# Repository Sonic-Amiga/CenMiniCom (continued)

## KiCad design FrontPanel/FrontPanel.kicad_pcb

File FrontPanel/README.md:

# Front panel board replica

# Modifications list.

1. Modern PSUs don't output any low voltage AC, and it's much easier to just generate
the frequency needed. For the purpose this board has a 555-based simple adjustable
clock generator instead of the original buffer/phase shifter circuit.

Russian characters in this file are using UTF-8 character set.

# Assembly notes

|Original       |Replacement            |
|---------------|-----------------------|
|74LS38		|К555ЛА13		|
|74LS123	|555АГ3		        |
|NE555		|К1441ВИ1		|

# Revision history.

30.11.2022 - rev 1.0

* Errarum E001: Incorrect ground and power separation

Current - rev 2.0

- Added decoupling capacitors
- Narrowed down while maintaining compatibility with original, mounting holes are kept in the same location
- Adjusted J3 footprint so that MPW-5 connector fits in

# Contacts

Please direct all questions to pavel_fedin@mail.ru

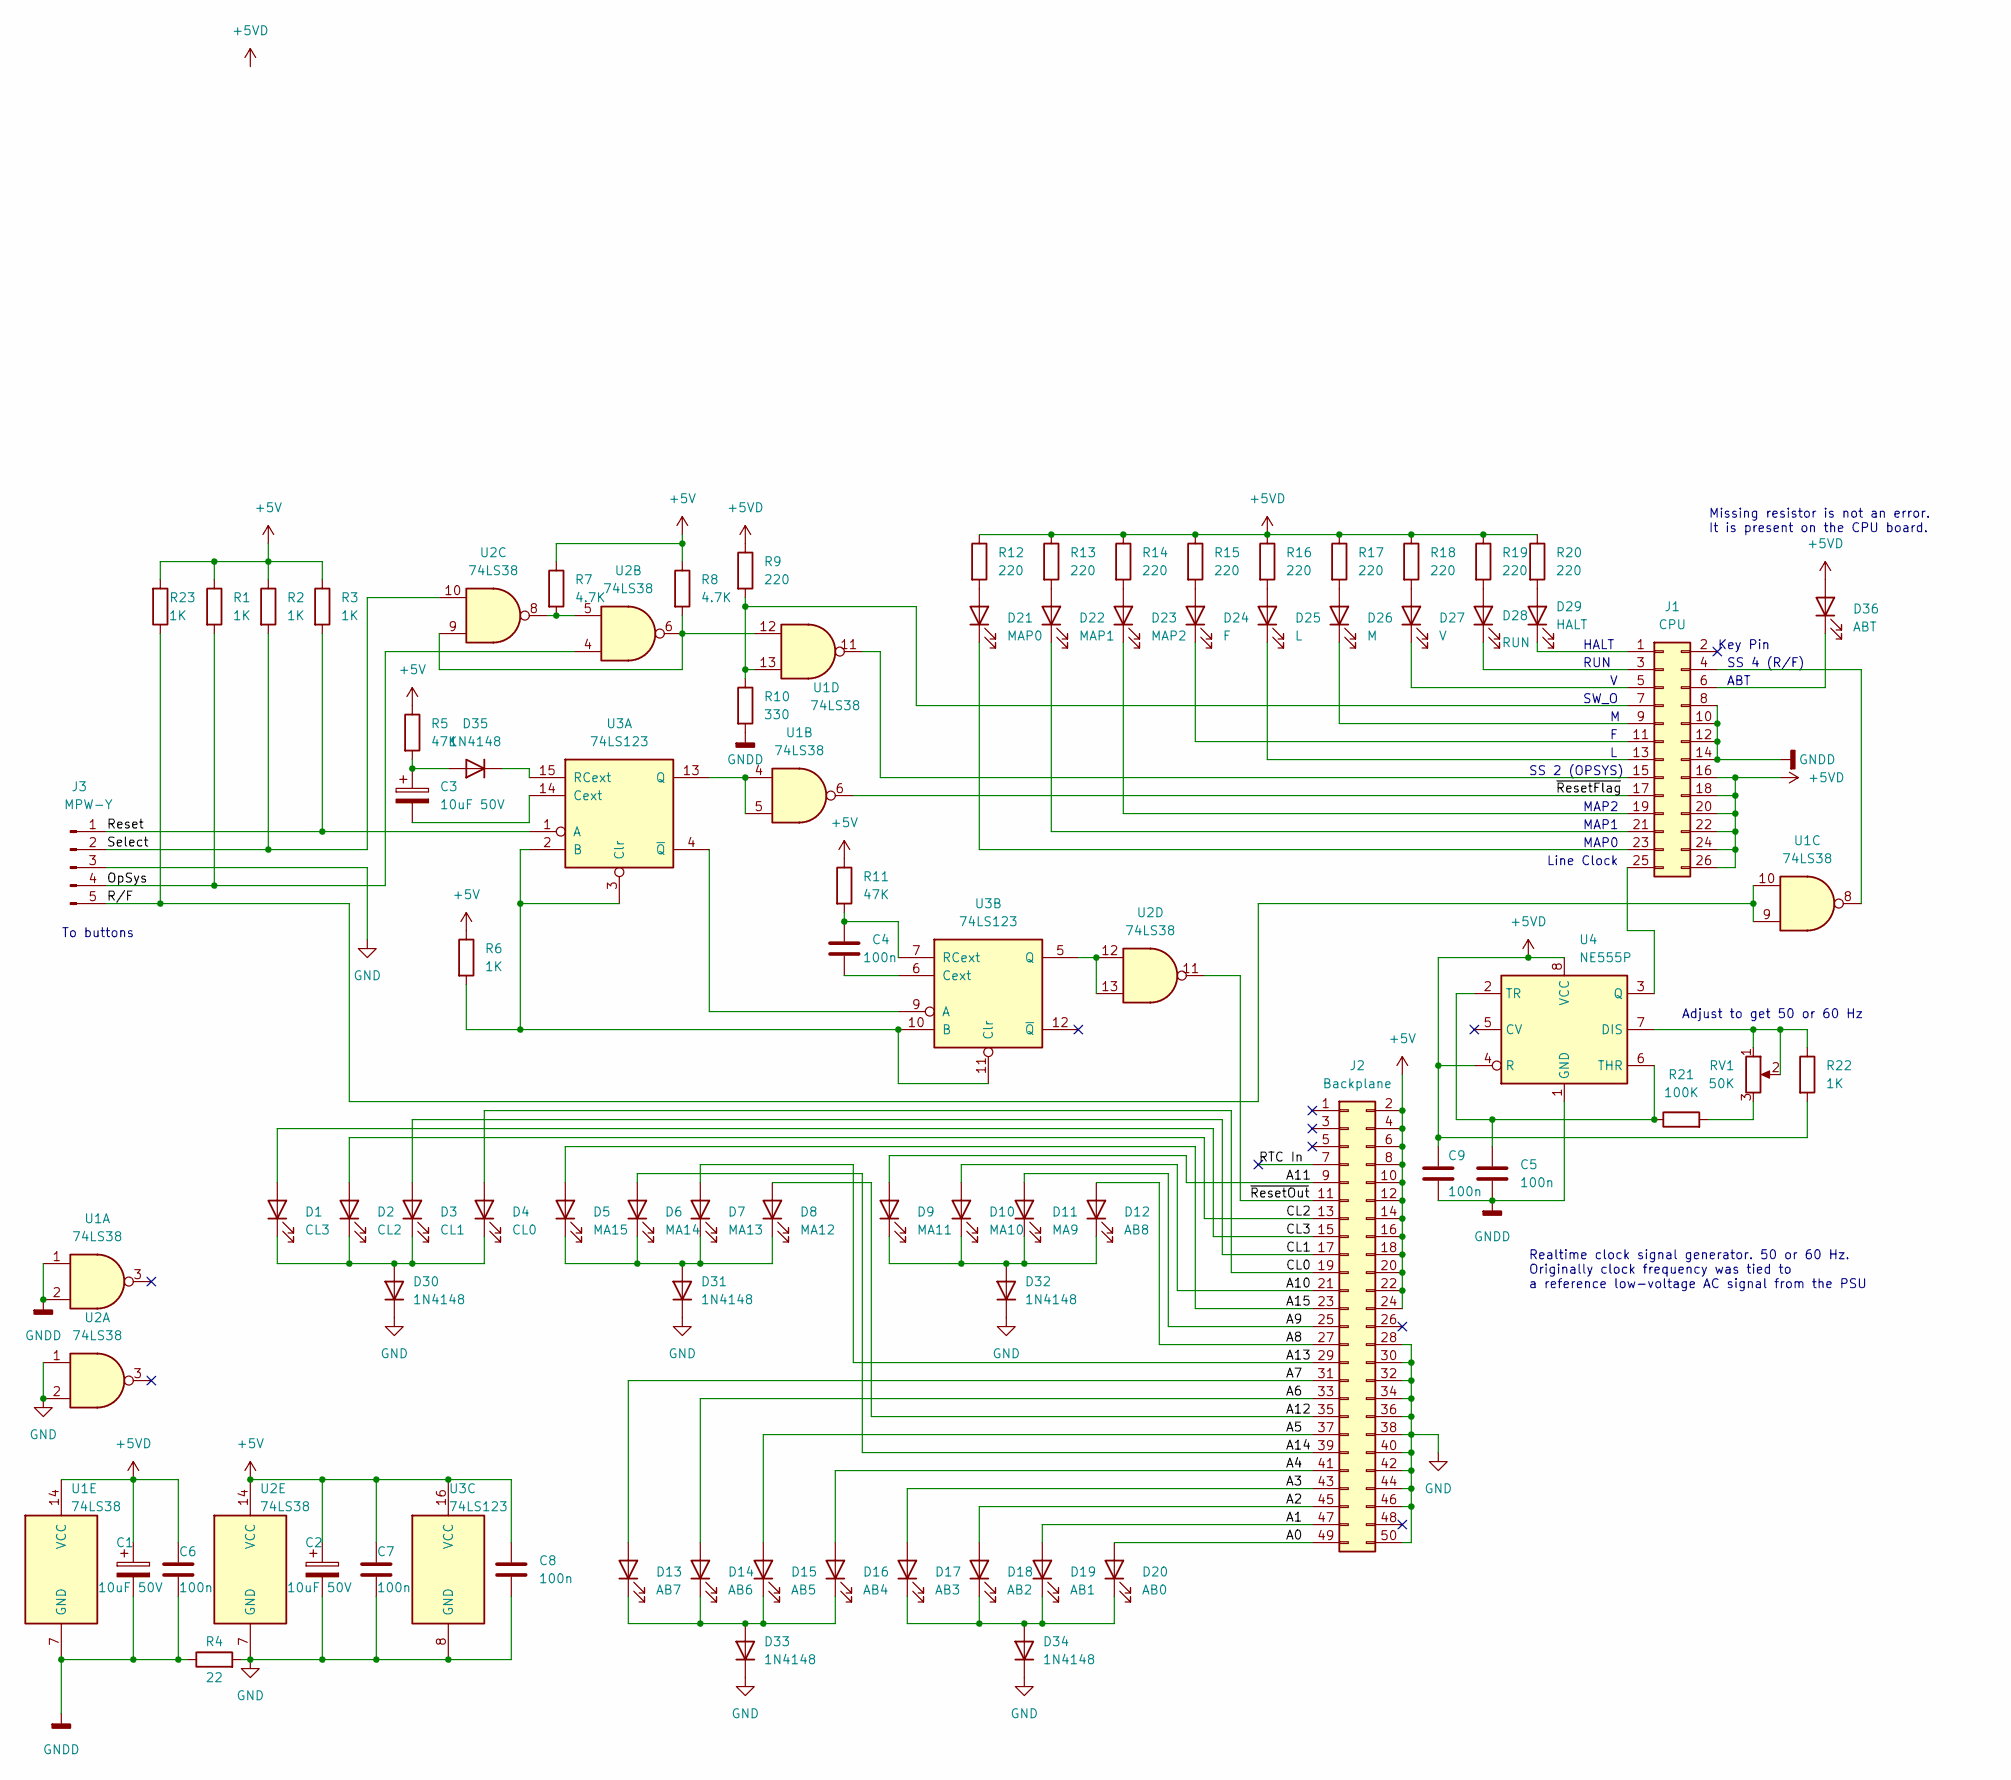
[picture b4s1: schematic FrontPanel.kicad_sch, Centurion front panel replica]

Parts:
C1, C2, C3: 10uF 50V; CP_Axial_L18.0mm_D6.5mm_P25.00mm_Horizontal
C4, C5, C6, C7, C8, C9: 100n; C_Disc_D4.3mm_W1.9mm_P5.00mm
D1: CL3; LED_D5.0mm
D2: CL2; LED_D5.0mm
D3: CL1; LED_D5.0mm
D4: CL0; LED_D5.0mm
D5: MA15; LED_D5.0mm
D6: MA14; LED_D5.0mm
D7: MA13; LED_D5.0mm
D8: MA12; LED_D5.0mm
D9: MA11; LED_D5.0mm
D10: MA10; LED_D5.0mm
D11: MA9; LED_D5.0mm
D12: AB8; LED_D5.0mm
D13: AB7; LED_D5.0mm
D14: AB6; LED_D5.0mm
D15: AB5; LED_D5.0mm
D16: AB4; LED_D5.0mm
D17: AB3; LED_D5.0mm
D18: AB2; LED_D5.0mm
D19: AB1; LED_D5.0mm
D20: AB0; LED_D5.0mm
D21: MAP0; LED_D5.0mm
D22: MAP1; LED_D5.0mm
D23: MAP2; LED_D5.0mm
D24: F; LED_D5.0mm
D25: L; LED_D5.0mm
D26: M; LED_D5.0mm
D27: V; LED_D5.0mm
D28: RUN; LED_D5.0mm
D29: HALT; LED_D5.0mm
D30, D31, D32, D33, D34, D35: 1N4148; D_A-405_P10.16mm_Horizontal
D36: ABT; LED_D5.0mm
J1: CPU; IDC-Header_2x13_P2.54mm_Vertical
J2: Backplane; IDC-Header_2x25_P2.54mm_Vertical
J3: MPW-Y; PhoenixContact_MSTBVA_2,5_5-G-5,08_1x05_P5.08mm_Vertical
R1, R2, R3, R6, R22, R23: 1K; R_Axial_DIN0207_L6.3mm_D2.5mm_P10.16mm_Horizontal
R4: 22; R_Axial_DIN0207_L6.3mm_D2.5mm_P10.16mm_Horizontal
R5, R11: 47K; R_Axial_DIN0207_L6.3mm_D2.5mm_P10.16mm_Horizontal
R7, R8: 4.7K; R_Axial_DIN0207_L6.3mm_D2.5mm_P10.16mm_Horizontal
R9, R12, R13, R14, R15, R16, R17, R18, R19, R20: 220; R_Axial_DIN0207_L6.3mm_D2.5mm_P10.16mm_Horizontal
R10: 330; R_Axial_DIN0207_L6.3mm_D2.5mm_P10.16mm_Horizontal
R21: 100K; R_Axial_DIN0207_L6.3mm_D2.5mm_P10.16mm_Horizontal
RV1: 50K; Potentiometer_Bourns_3299Y_Vertical
U1, U2: 74LS38; DIP-14_W7.62mm
U3: 74LS123; DIP-16_W7.62mm
U4: NE555P; DIP-8_W7.62mm

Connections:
+5V: C2.1, C7.1, C8.1, J2.2, J2.4, J2.6, J2.8, J2.10, J2.12, J2.14, J2.16, J2.18, J2.20, J2.22, J2.24, R1.1, R2.1, R3.1, R5.1, R6.1, R7.1, R8.1, R11.1, R23.2, U2.14 (VCC), U3.16 (VCC)
+5VD: C1.1, C6.1, C9.1, D36.2 (A), J1.16, J1.18, J1.20, J1.22, J1.24, J1.26, R9.1, R12.1, R13.1, R14.1, R15.1, R16.1, R17.1, R18.1, R19.1, R20.1, R22.2, U1.14 (VCC), U4.4 (R), U4.8 (VCC)
/A0: D20.2 (A), J2.49
/A1: D19.2 (A), J2.47
/A2: D18.2 (A), J2.45
/A3: D17.2 (A), J2.43
/A4: D16.2 (A), J2.41
/A5: D15.2 (A), J2.37
/A6: D14.2 (A), J2.33
/A7: D13.2 (A), J2.31
/A8: D12.2 (A), J2.27
/A9: D11.2 (A), J2.25
/A10: D10.2 (A), J2.21
/A11: D9.2 (A), J2.9
/A12: D8.2 (A), J2.35
/A13: D7.2 (A), J2.29
/A14: D6.2 (A), J2.39
/A15: D5.2 (A), J2.23
/CL0: D4.2 (A), J2.19
/CL1: D3.2 (A), J2.17
/CL2: D2.2 (A), J2.13
/CL3: D1.2 (A), J2.15
/OpSys: J3.4, R1.2, U2.4
/RTC In: J2.7
/Reset: J3.1, R3.2, U3.1 (A)
/R/F: J3.5, R23.1, U1.9, U1.10
/Select: J3.2, R2.2, U2.10
/~ResetFlag: J1.17, U1.6
/~ResetOut: J2.11, U2.11
GND: C2.2, C7.2, C8.2, D30.1 (K), D31.1 (K), D32.1 (K), D33.1 (K), D34.1 (K), J2.28, J2.30, J2.32, J2.34, J2.36, J2.38, J2.40, J2.42, J2.44, J2.46, J2.50, J3.3, R4.2, U2.1, U2.2, U2.7 (GND), U3.8 (GND)
GNDD: C1.2, C5.2, C6.2, C9.2, J1.8, J1.10, J1.12, J1.14, R4.1, R10.2, U1.1, U1.2, U1.7 (GND), U4.1 (GND)
unnamed: C3.1, D35.2 (A), R5.2
unnamed: C3.2, U3.14 (Cext)
unnamed: C4.1, R11.2, U3.7 (RCext)
unnamed: C4.2, U3.6 (Cext)
unnamed: C5.1, R21.1, U4.2 (TR), U4.6 (THR)
unnamed: D1.1 (K), D2.1 (K), D3.1 (K), D4.1 (K), D30.2 (A)
unnamed: D9.1 (K), D10.1 (K), D11.1 (K), D12.1 (K), D32.2 (A)
unnamed: D13.1 (K), D14.1 (K), D15.1 (K), D16.1 (K), D33.2 (A)
unnamed: D17.1 (K), D18.1 (K), D19.1 (K), D20.1 (K), D34.2 (A)
unnamed: D21.1 (K), J1.23
unnamed: D21.2 (A), R12.2
unnamed: D22.1 (K), J1.21
unnamed: D22.2 (A), R13.2
unnamed: D23.1 (K), J1.19
unnamed: D23.2 (A), R14.2
unnamed: D24.1 (K), J1.11
unnamed: D24.2 (A), R15.2
unnamed: D25.1 (K), J1.13
unnamed: D25.2 (A), R16.2
unnamed: D26.1 (K), J1.9
unnamed: D26.2 (A), R17.2
unnamed: D27.1 (K), J1.5
unnamed: D27.2 (A), R18.2
unnamed: D28.1 (K), J1.3
unnamed: D28.2 (A), R19.2
unnamed: D29.1 (K), J1.1
unnamed: D29.2 (A), R20.2
unnamed: D5.1 (K), D6.1 (K), D7.1 (K), D8.1 (K), D31.2 (A)
unnamed: D35.1 (K), U3.15 (RCext)
unnamed: D36.1 (K), J1.6
unnamed: J1.4, U1.8
unnamed: J1.7, R9.2, R10.1, U1.13
unnamed: J1.15, U1.11
unnamed: J1.25, U4.3 (Q)
unnamed: R6.2, U3.2 (B), U3.3 (Clr), U3.10 (B), U3.11 (Clr)
unnamed: R7.2, U2.5, U2.8
unnamed: R8.2, U1.12, U2.6, U2.9
unnamed: R21.2, RV1.3
unnamed: R22.1, RV1.1, RV1.2, U4.7 (DIS)
unnamed: U1.4, U1.5, U3.13 (Q)
unnamed: U2.12, U2.13, U3.5 (Q)
unnamed: U3.4 (~Q), U3.9 (A)

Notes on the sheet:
RUN
Realtime clock signal generator. 50 or 60 Hz. Originally clock frequency was tied to a reference low-voltage AC signal from the PSU
MAP1
HALT
Key Pin
Missing resistor is not an error. It is present on the CPU board.
SS 2 (OPSYS)
Adjust to get 50 or 60 Hz
SS 4 (R/F)
ABT
Line Clock
SW_O
MAP0
To buttons
MAP2

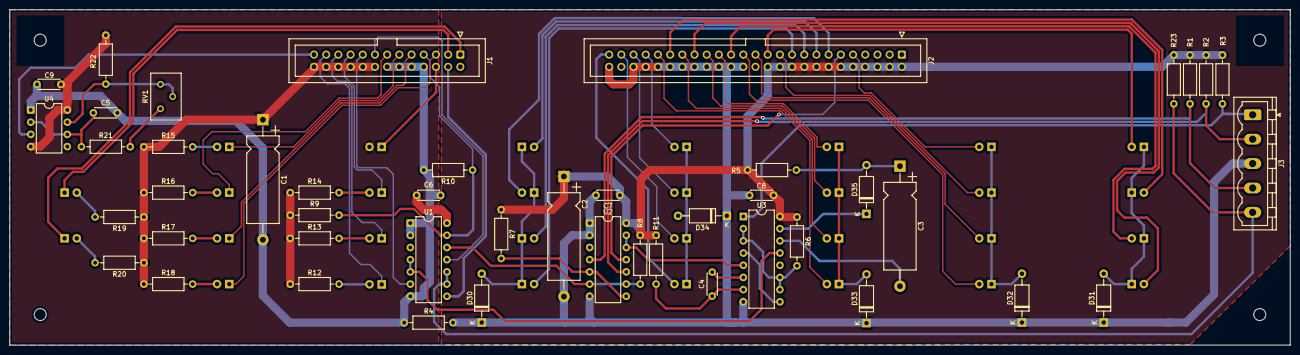
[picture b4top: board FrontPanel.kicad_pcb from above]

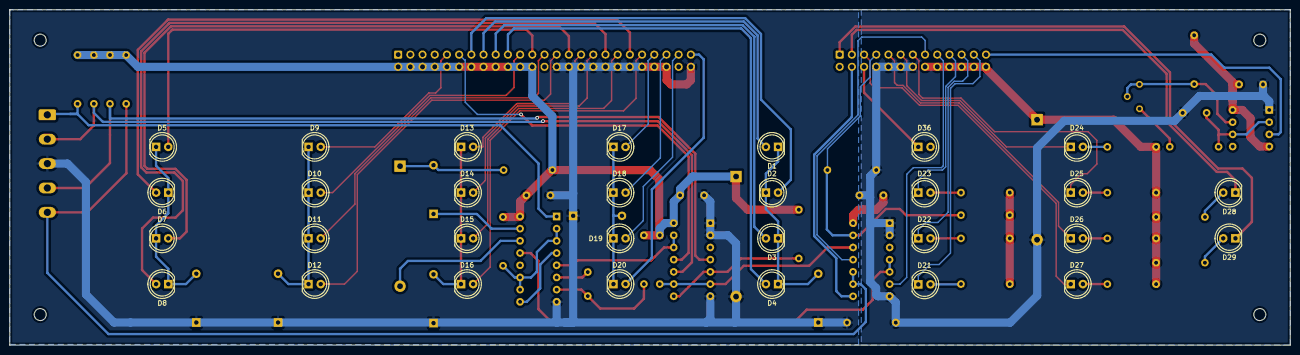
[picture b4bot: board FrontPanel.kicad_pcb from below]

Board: 2 copper layers, 266.7 x 69.8 mm, 76 parts (30 on the bottom side), 72 nets.
